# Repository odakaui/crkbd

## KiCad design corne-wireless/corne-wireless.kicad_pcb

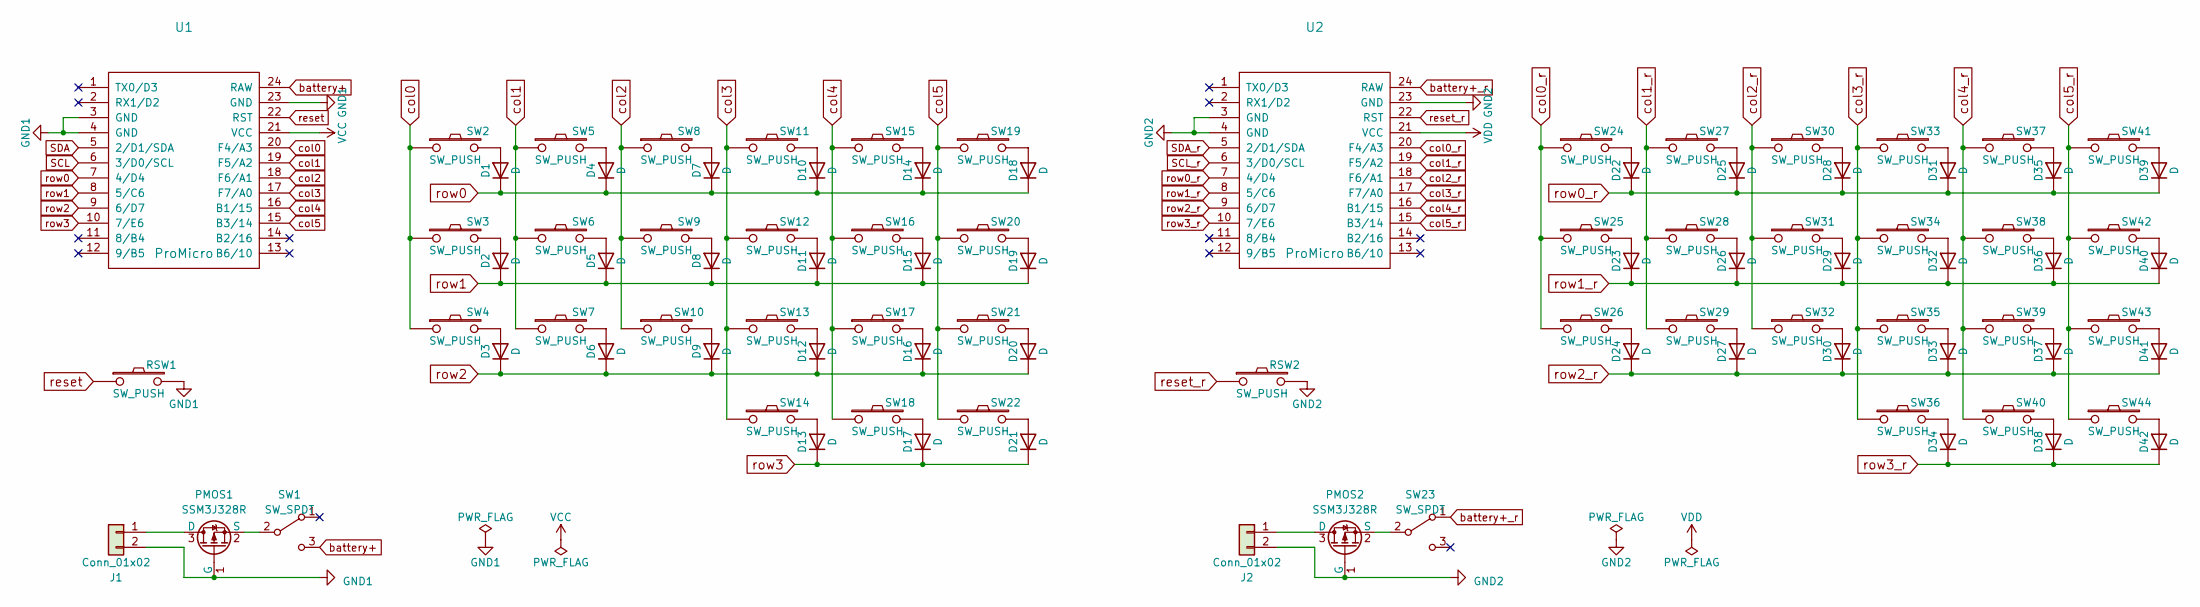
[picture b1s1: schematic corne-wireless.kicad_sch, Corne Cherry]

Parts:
D1, D2, D3, D4, D5, D6, D7, D8, D9, D10, D11, D12, D13, D14, D15, D16, D17, D18, D19, D20, D21, D22, D23, D24, D25, D26, D27, D28, D29, D30, D31, D32, D33, D34, D35, D36, D37, D38, D39, D40, D41, D42: D; D3_SMD_v2
J1, J2: Conn_01x02; JST_PH_B2B-PH-K_1x02_P2.00mm_Vertical
PMOS1, PMOS2: SSM3J328R; SOT-23F
RSW1, RSW2: SW_PUSH; ResetSW_1side
SW1, SW23: SW_SPDT; SW_SPDT_PCM12
SW2, SW3, SW4, SW5, SW6, SW7, SW8, SW9, SW10, SW11, SW12, SW13, SW14, SW15, SW16, SW17, SW18, SW19, SW20, SW21, SW24, SW25, SW26, SW27, SW28, SW29, SW30, SW31, SW32, SW33, SW34, SW35, SW36, SW37, SW38, SW39, SW40, SW41, SW42, SW43: SW_PUSH; CherryMX_Hotswap
SW22, SW44: SW_PUSH; CherryMX_Hotswap_1.5u
U1, U2: ProMicro; ProMicro_v3

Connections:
GND1: J1.2, PMOS1.1 (G), RSW1.2, U1.3 (GND), U1.4 (GND), U1.23 (GND)
GND2: J2.2, PMOS2.1 (G), RSW2.2, U2.3 (GND), U2.4 (GND), U2.23 (GND)
unnamed: D1.2 (A), SW2.2
unnamed: D2.2 (A), SW3.2
unnamed: D3.2 (A), SW4.2
unnamed: D4.2 (A), SW5.2
unnamed: D5.2 (A), SW6.2
unnamed: D6.2 (A), SW7.2
unnamed: D7.2 (A), SW8.2
unnamed: D8.2 (A), SW9.2
unnamed: D9.2 (A), SW10.2
unnamed: D10.2 (A), SW11.2
unnamed: D11.2 (A), SW12.2
unnamed: D12.2 (A), SW13.2
unnamed: D13.2 (A), SW14.2
unnamed: D14.2 (A), SW15.2
unnamed: D15.2 (A), SW16.2
unnamed: D16.2 (A), SW17.2
unnamed: D17.2 (A), SW18.2
unnamed: D18.2 (A), SW19.2
unnamed: D19.2 (A), SW20.2
unnamed: D20.2 (A), SW21.2
unnamed: D21.2 (A), SW22.2
unnamed: D22.2 (A), SW24.2
unnamed: D23.2 (A), SW25.2
unnamed: D24.2 (A), SW26.2
unnamed: D25.2 (A), SW27.2
unnamed: D26.2 (A), SW28.2
unnamed: D27.2 (A), SW29.2
unnamed: D28.2 (A), SW30.2
unnamed: D29.2 (A), SW31.2
unnamed: D30.2 (A), SW32.2
unnamed: D31.2 (A), SW33.2
unnamed: D32.2 (A), SW34.2
unnamed: D33.2 (A), SW35.2
unnamed: D34.2 (A), SW36.2
unnamed: D35.2 (A), SW37.2
unnamed: D36.2 (A), SW38.2
unnamed: D37.2 (A), SW39.2
unnamed: D38.2 (A), SW40.2
unnamed: D39.2 (A), SW41.2
unnamed: D40.2 (A), SW42.2
unnamed: D41.2 (A), SW43.2
unnamed: D42.2 (A), SW44.2
unnamed: J1.1, PMOS1.3 (D)
unnamed: J2.1, PMOS2.3 (D)
unnamed: PMOS1.2 (S), SW1.2 (B)
unnamed: PMOS2.2 (S), SW23.2 (B)
SCL: U1.6 (3/D0/SCL)
SCL_r: U2.6 (3/D0/SCL)
SDA: U1.5 (2/D1/SDA)
SDA_r: U2.5 (2/D1/SDA)
VCC: U1.21 (VCC)
VDD: U2.21 (VCC)
battery+: SW1.3 (C), U1.24 (RAW)
battery+_r: SW23.1 (A), U2.24 (RAW)
col0: SW2.1, SW3.1, SW4.1, U1.20 (F4/A3)
col0_r: SW24.1, SW25.1, SW26.1, U2.20 (F4/A3)
col1: SW5.1, SW6.1, SW7.1, U1.19 (F5/A2)
col1_r: SW27.1, SW28.1, SW29.1, U2.19 (F5/A2)
col2: SW8.1, SW9.1, SW10.1, U1.18 (F6/A1)
col2_r: SW30.1, SW31.1, SW32.1, U2.18 (F6/A1)
col3: SW11.1, SW12.1, SW13.1, SW14.1, U1.17 (F7/A0)
col3_r: SW33.1, SW34.1, SW35.1, SW36.1, U2.17 (F7/A0)
col4: SW15.1, SW16.1, SW17.1, SW18.1, U1.16 (B1/15)
col4_r: SW37.1, SW38.1, SW39.1, SW40.1, U2.16 (B1/15)
col5: SW19.1, SW20.1, SW21.1, SW22.1, U1.15 (B3/14)
col5_r: SW41.1, SW42.1, SW43.1, SW44.1, U2.15 (B3/14)
reset: RSW1.1, U1.22 (RST)
reset_r: RSW2.1, U2.22 (RST)
row0: D1.1 (K), D4.1 (K), D7.1 (K), D10.1 (K), D14.1 (K), D18.1 (K), U1.7 (4/D4)
row0_r: D22.1 (K), D25.1 (K), D28.1 (K), D31.1 (K), D35.1 (K), D39.1 (K), U2.7 (4/D4)
row1: D2.1 (K), D5.1 (K), D8.1 (K), D11.1 (K), D15.1 (K), D19.1 (K), U1.8 (5/C6)
row1_r: D23.1 (K), D26.1 (K), D29.1 (K), D32.1 (K), D36.1 (K), D40.1 (K), U2.8 (5/C6)
row2: D3.1 (K), D6.1 (K), D9.1 (K), D12.1 (K), D16.1 (K), D20.1 (K), U1.9 (6/D7)
row2_r: D24.1 (K), D27.1 (K), D30.1 (K), D33.1 (K), D37.1 (K), D41.1 (K), U2.9 (6/D7)
row3: D13.1 (K), D17.1 (K), D21.1 (K), U1.10 (7/E6)
row3_r: D34.1 (K), D38.1 (K), D42.1 (K), U2.10 (7/E6)

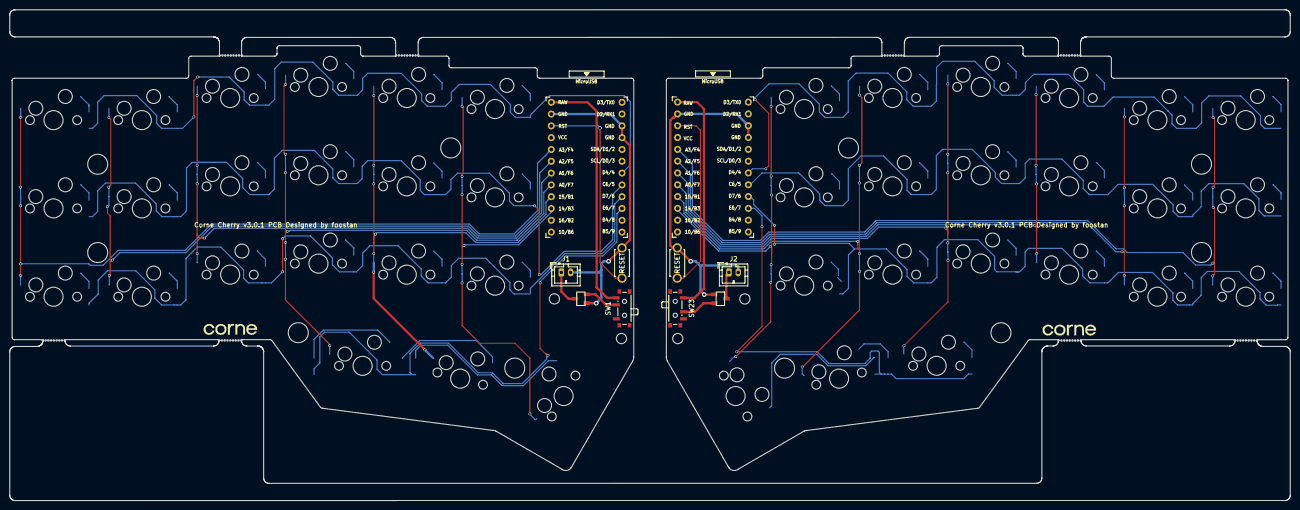
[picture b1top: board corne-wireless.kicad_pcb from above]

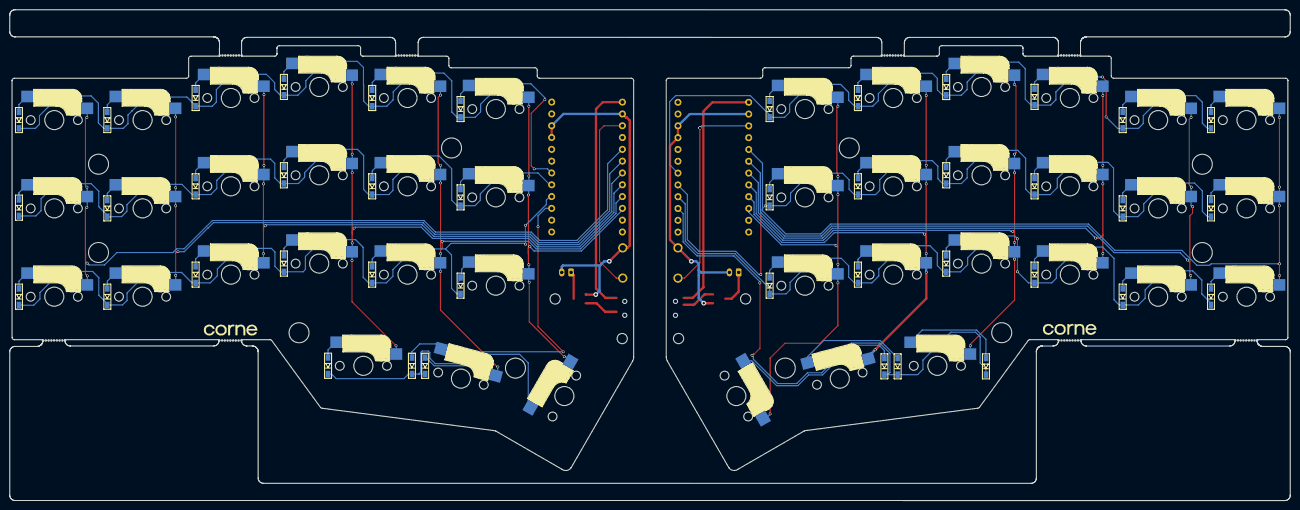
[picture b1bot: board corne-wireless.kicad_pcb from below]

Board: 2 copper layers, 275.5 x 105.6 mm, 108 parts (45 on the bottom side), 72 nets.

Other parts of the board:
Ref**: Val**; M2_HOLE_v2
Ref**#2, Ref**#3, Ref**#4, Ref**#5, Ref**#6, Ref**#7, Ref**#8, Ref**#9, Ref**#10, Ref**#11, Ref**#12, Ref**#13, Ref**#14: Val**; M2_HOLE_v2

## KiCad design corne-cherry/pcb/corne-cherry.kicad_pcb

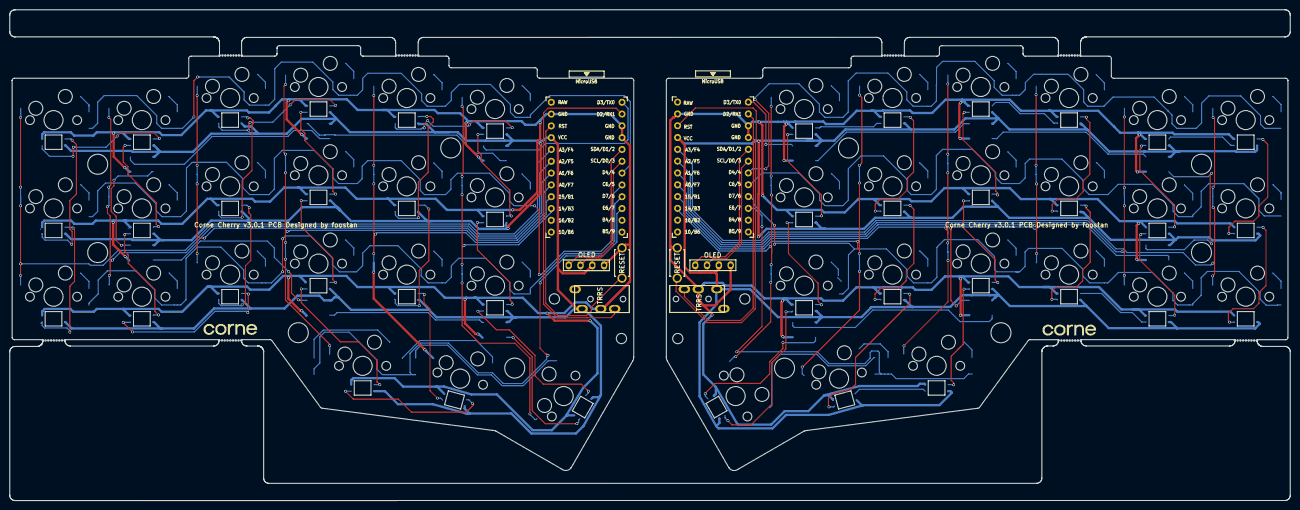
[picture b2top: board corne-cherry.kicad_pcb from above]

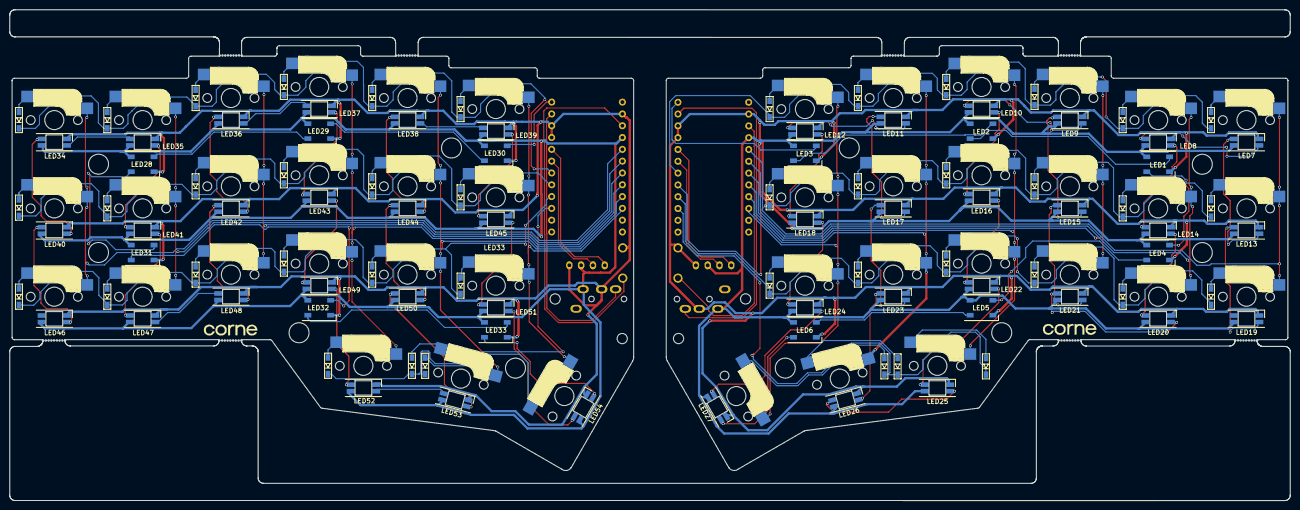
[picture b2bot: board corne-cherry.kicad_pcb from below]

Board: 2 copper layers, 275.5 x 105.6 mm, 160 parts (99 on the bottom side), 128 nets.

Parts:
D1, D2, D3, D4, D5, D6, D7, D8, D9, D10, D11, D12, D13, D14, D15, D16, D17, D18, D19, D20, D21, D22, D23, D24, D25, D26, D27, D28, D29, D30, D31, D32, D33, D34, D35, D36, D37, D38, D39, D40, D41, D42: D; D3_SMD_v2
J1, J3: MJ-4PP-9; MJ-4PP-9_1side
J2, J4: OLED; OLED_1side
LED1, LED2, LED3, LED4, LED5, LED6, LED28, LED29, LED30, LED31, LED32, LED33: WS2812B; LED_WS2812B_PLCC4_5.0x5.0mm_P3.2mm
LED7, LED8, LED9, LED10, LED11, LED12, LED13, LED14, LED15, LED16, LED17, LED18, LED19, LED20, LED21, LED22, LED23, LED24, LED25, LED26, LED27, LED34, LED35, LED36, LED37, LED38, LED39, LED40, LED41, LED42, LED43, LED44, LED45, LED46, LED47, LED48, LED49, LED50, LED51, LED52, LED53, LED54: YS-SK6812MINI-E
RSW1, RSW2: SW_PUSH; ResetSW_1side
Ref**: Val**; M2_HOLE_v2
Ref**#2, Ref**#3, Ref**#4, Ref**#5, Ref**#6, Ref**#7, Ref**#8, Ref**#9, Ref**#10, Ref**#11, Ref**#12, Ref**#13, Ref**#14: Val**; M2_HOLE_v2
SW1, SW2, SW3, SW4, SW5, SW6, SW7, SW8, SW9, SW10, SW11, SW12, SW13, SW14, SW15, SW16, SW17, SW18, SW19, SW20, SW22, SW23, SW24, SW25, SW26, SW27, SW28, SW29, SW30, SW31, SW32, SW33, SW34, SW35, SW36, SW37, SW38, SW39, SW40, SW41: SW_PUSH; CherryMX_Hotswap
SW21, SW42: SW_PUSH; CherryMX_Hotswap_1.5u
U1, U2: ProMicro; ProMicro_v3

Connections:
GND: J1.C, J2.4, LED1.3, LED2.3, LED3.3, LED4.3, LED5.3, LED6.3, LED7.3, LED8.3, LED9.3, LED10.3, LED11.3, LED12.3, LED13.3, LED14.3, LED15.3, LED16.3, LED17.3, LED18.3, LED19.3, LED20.3, LED21.3, LED22.3, LED23.3, LED24.3, LED25.3, LED26.3, LED27.3, RSW1.2, U1.3, U1.4, U1.23
GNDA: J3.C, J4.4, LED28.3, LED29.3, LED30.3, LED31.3, LED32.3, LED33.3, LED34.3, LED35.3, LED36.3, LED37.3, LED38.3, LED39.3, LED40.3, LED41.3, LED42.3, LED43.3, LED44.3, LED45.3, LED46.3, LED47.3, LED48.3, LED49.3, LED50.3, LED51.3, LED52.3, LED53.3, LED54.3, RSW2.2, U2.3, U2.4, U2.23
LED: LED3.4, U1.1
LED_r: LED30.4, U2.1
unnamed: D1.2, SW1.2
unnamed: D2.2, SW2.2
unnamed: D3.2, SW3.2
unnamed: D4.2, SW4.2
unnamed: D5.2, SW5.2
unnamed: D6.2, SW6.2
unnamed: D7.2, SW7.2
unnamed: D8.2, SW8.2
unnamed: D9.2, SW9.2
unnamed: D10.2, SW10.2
unnamed: D11.2, SW11.2
unnamed: D12.2, SW12.2
unnamed: D13.2, SW13.2
unnamed: D14.2, SW14.2
unnamed: D15.2, SW15.2
unnamed: D16.2, SW16.2
unnamed: D17.2, SW17.2
unnamed: D18.2, SW18.2
unnamed: D19.2, SW19.2
unnamed: D20.2, SW20.2
unnamed: D21.2, SW21.2
unnamed: D22.2, SW22.2
unnamed: D23.2, SW23.2
unnamed: D24.2, SW24.2
unnamed: D25.2, SW25.2
unnamed: D26.2, SW26.2
unnamed: D27.2, SW27.2
unnamed: D28.2, SW28.2
unnamed: D29.2, SW29.2
unnamed: D30.2, SW30.2
unnamed: D31.2, SW31.2
unnamed: D32.2, SW32.2
unnamed: D33.2, SW33.2
unnamed: D34.2, SW34.2
unnamed: D35.2, SW35.2
unnamed: D36.2, SW36.2
unnamed: D37.2, SW37.2
unnamed: D38.2, SW38.2
unnamed: D39.2, SW39.2
unnamed: D40.2, SW40.2
unnamed: D41.2, SW41.2
unnamed: D42.2, SW42.2
unnamed: LED1.2, LED4.4
unnamed: LED1.4, LED2.2
unnamed: LED2.4, LED3.2
unnamed: LED4.2, LED5.4
unnamed: LED5.2, LED6.4
unnamed: LED7.4, LED8.2
unnamed: LED9.4, LED10.2
unnamed: LED10.4, LED16.2
unnamed: LED11.2, LED17.4
unnamed: LED11.4, LED12.2
unnamed: LED12.4, LED18.2
unnamed: LED13.2, LED19.4
unnamed: LED7.2, LED13.4
unnamed: LED8.4, LED14.2
unnamed: LED14.4, LED20.2
unnamed: LED15.2, LED21.4
unnamed: LED9.2, LED15.4
unnamed: LED16.4, LED22.2
unnamed: LED17.2, LED23.4
unnamed: LED18.4, LED24.2
unnamed: LED20.4, LED21.2
unnamed: LED22.4, LED25.2
unnamed: LED23.2, LED26.4
unnamed: LED24.4, LED27.2
unnamed: LED25.4, LED26.2
unnamed: LED6.2, LED27.4
unnamed: LED28.2, LED31.4
unnamed: LED28.4, LED29.2
unnamed: LED29.4, LED30.2
unnamed: LED31.2, LED32.4
unnamed: LED32.2, LED33.4
unnamed: LED33.2, LED54.4
unnamed: LED34.2, LED40.4
unnamed: LED34.4, LED35.2
unnamed: LED35.4, LED41.2
unnamed: LED36.2, LED42.4
unnamed: LED36.4, LED37.2
unnamed: LED37.4, LED43.2
unnamed: LED38.2, LED44.4
unnamed: LED38.4, LED39.2
unnamed: LED39.4, LED45.2
unnamed: LED40.2, LED46.4
unnamed: LED41.4, LED47.2
unnamed: LED42.2, LED48.4
unnamed: LED43.4, LED49.2
unnamed: LED44.2, LED50.4
unnamed: LED45.4, LED51.2
unnamed: LED47.4, LED48.2
unnamed: LED49.4, LED52.2
unnamed: LED50.2, LED53.4
unnamed: LED51.4, LED54.2
unnamed: LED52.4, LED53.2
SCL: J2.2, U1.6
SCL_r: J4.2, U2.6
SDA: J2.1, U1.5
SDA_r: J4.1, U2.5
VCC: J1.D, J2.3, LED1.1, LED2.1, LED3.1, LED4.1, LED5.1, LED6.1, LED7.1, LED8.1, LED9.1, LED10.1, LED11.1, LED12.1, LED13.1, LED14.1, LED15.1, LED16.1, LED17.1, LED18.1, LED19.1, LED20.1, LED21.1, LED22.1, LED23.1, LED24.1, LED25.1, LED26.1, LED27.1, U1.21
VDD: J3.D, J4.3, LED28.1, LED29.1, LED30.1, LED31.1, LED32.1, LED33.1, LED34.1, LED35.1, LED36.1, LED37.1, LED38.1, LED39.1, LED40.1, LED41.1, LED42.1, LED43.1, LED44.1, LED45.1, LED46.1, LED47.1, LED48.1, LED49.1, LED50.1, LED51.1, LED52.1, LED53.1, LED54.1, U2.21
col0: SW1.1, SW7.1, SW13.1, U1.20
col0_r: SW22.1, SW28.1, SW34.1, U2.20
col1: SW2.1, SW8.1, SW14.1, U1.19
col1_r: SW23.1, SW29.1, SW35.1, U2.19
col2: SW3.1, SW9.1, SW15.1, U1.18
col2_r: SW24.1, SW30.1, SW36.1, U2.18
col3: SW4.1, SW10.1, SW16.1, SW19.1, U1.17
col3_r: SW25.1, SW31.1, SW37.1, SW40.1, U2.17
col4: SW5.1, SW11.1, SW17.1, SW20.1, U1.16
col4_r: SW26.1, SW32.1, SW38.1, SW41.1, U2.16
col5: SW6.1, SW12.1, SW18.1, SW21.1, U1.15
col5_r: SW27.1, SW33.1, SW39.1, SW42.1, U2.15
data: J1.B, U1.2
data_r: J3.B, U2.2
reset: RSW1.1, U1.22
reset_r: RSW2.1, U2.22
row0: D1.1, D2.1, D3.1, D4.1, D5.1, D6.1, U1.7
row0_r: D22.1, D23.1, D24.1, D25.1, D26.1, D27.1, U2.7
row1: D7.1, D8.1, D9.1, D10.1, D11.1, D12.1, U1.8
row1_r: D28.1, D29.1, D30.1, D31.1, D32.1, D33.1, U2.8
row2: D13.1, D14.1, D15.1, D16.1, D17.1, D18.1, U1.9
row2_r: D34.1, D35.1, D36.1, D37.1, D38.1, D39.1, U2.9
row3: D19.1, D20.1, D21.1, U1.10
row3_r: D40.1, D41.1, D42.1, U2.10

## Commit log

2023-03-23 Migrate to Kicad 7.0
2023-03-23 Fix symbols on schematic WIP
2023-03-24 Restart
2023-03-26 Prep for removal of OLED headers
2023-03-26 Finalize PCB
2023-03-29 Change JST SH connector to PH
2023-03-30 Change gerber output directory
2023-04-18 Update kicad_prl
